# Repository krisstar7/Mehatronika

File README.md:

# GEMS Amethyst

---

- The **Proekt** folder is the **main project folder** containing all the KiCAD files you need.  
- The **Porocilo** folder holds the LaTeX source code for the report.  
- For the complete report, please check out **Mehatronika.pdf**.

---

- Mapa **Proekt** je **glavna projektna mapa**, ki vsebuje vse KiCAD datoteke.  
- Mapa **Porocilo** vsebuje LaTeX izvorno kodo za poročilo.  
- Celotno poročilo najdete v datoteki **Mehatronika.pdf**.

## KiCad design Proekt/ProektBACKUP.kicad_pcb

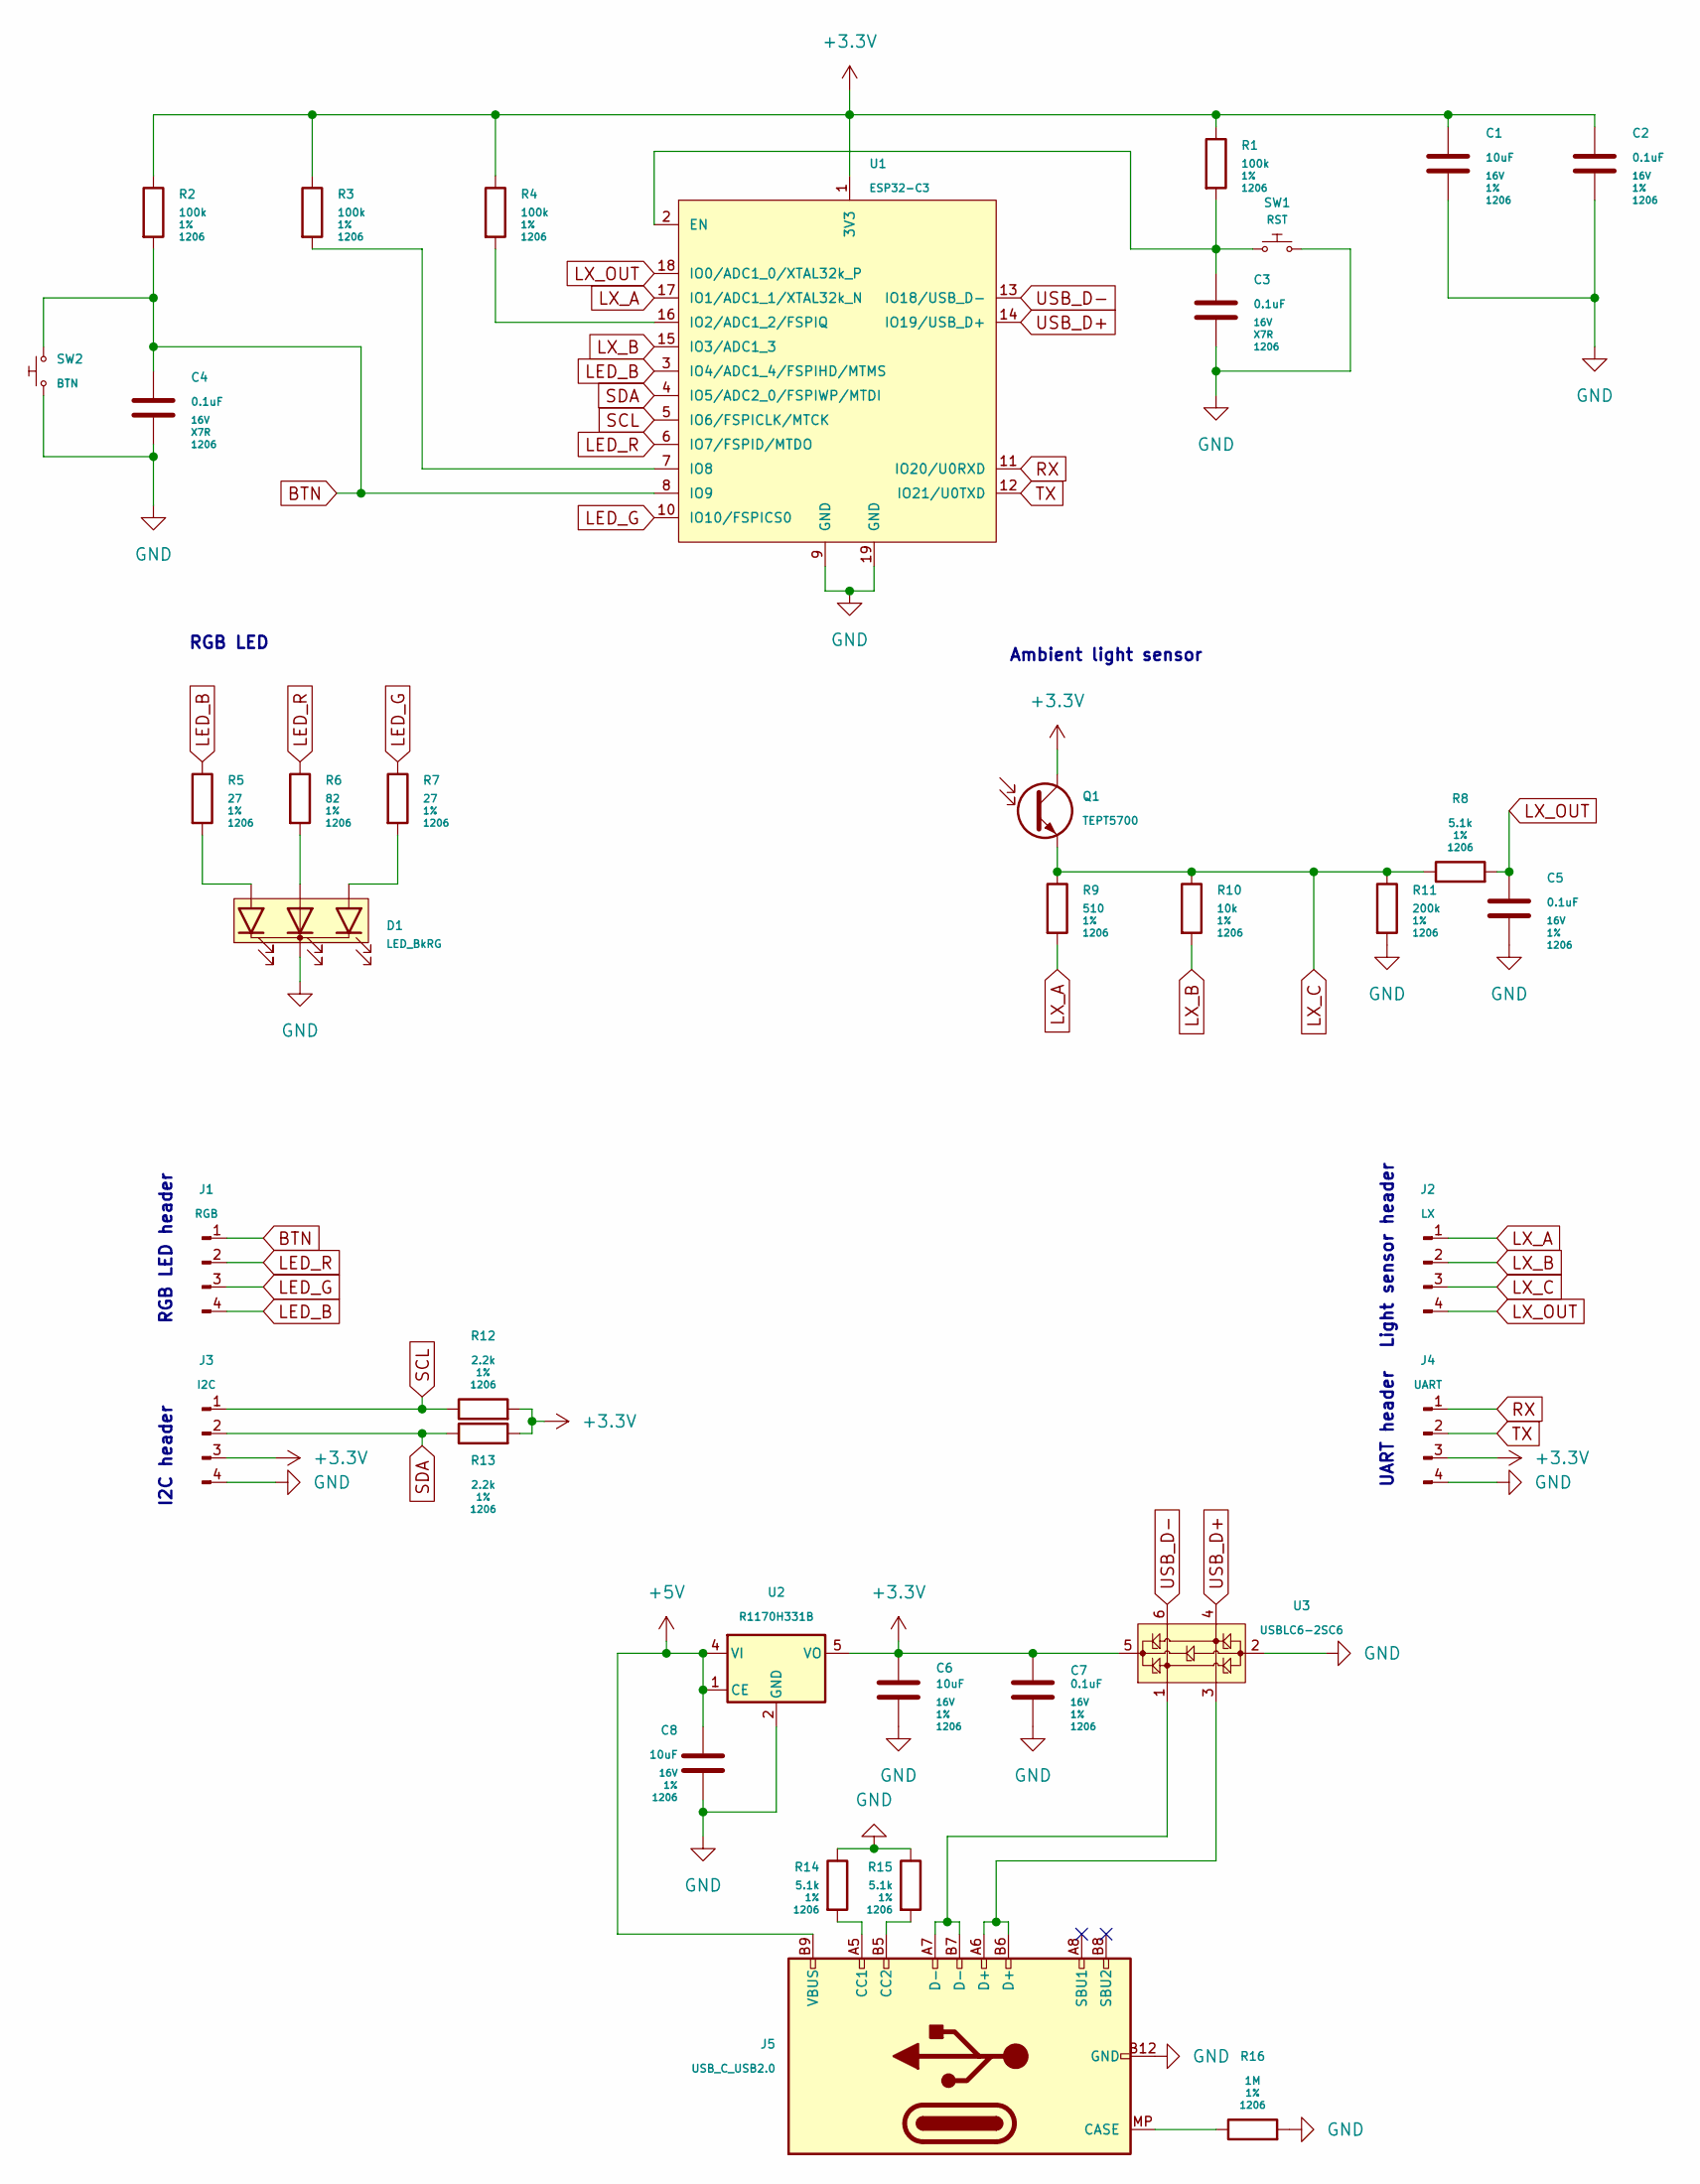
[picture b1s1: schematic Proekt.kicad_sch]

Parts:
C1, C6, C8: 10uF; C_1206_(3216); Voltage 16V; Tolerance 1%
C2, C5, C7: 0.1uF; C_1206_(3216); Voltage 16V; Tolerance 1%
C3, C4: 0.1uF; C_1206_(3216); Voltage 16V; Tolerance X7R
D1: LED_BkRG; LED_D5.0mm-4_RGB
J1: RGB; PinHeader_1x04_P2.54mm_Vertical
J2: LX; PinHeader_1x04_P2.54mm_Vertical
J3: I2C; PinHeader_1x04_P2.54mm_Vertical
J4: UART; PinHeader_1x04_P2.54mm_Vertical
J5: USB_C_USB2.0; USB-C_MOLEX-216990-0001
Q1: TEPT5700; PT_D5.0mm
R1, R2, R3, R4: 100k; R_1206_(3216); Tolerance 1%
R5, R7: 27; R_1206_(3216); Tolerance 1%
R6: 82; R_1206_(3216); Tolerance 1%
R8, R14, R15: 5.1k; R_1206_(3216); Tolerance 1%
R9: 510; R_1206_(3216); Tolerance 1%
R10: 10k; R_1206_(3216); Tolerance 1%
R11: 200k; R_1206_(3216); Tolerance 1%
R12, R13: 2.2k; R_1206_(3216); Tolerance 1%
R16: 1M; R_1206_(3216); Tolerance 1%
SW1: RST; SW_PUSH_6mm_SMD
SW2: BTN; SW_PUSH_6mm_SMD
U1: ESP32-C3; ESP32-C3-WROOM-02
U2: R1170H331B; SOT-89-5
U3: USBLC6-2SC6; SOT-23-6

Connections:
+3.3V: C1.1, C2.1, C6.1, C7.1, J3.3, J4.3, Q1.C, R1.1, R2.1, R3.1, R4.1, R12.2, R13.2, U1.1 (3V3), U2.5 (VO), U3.5 (VBUS)
+5V: C8.1, J5.A4 (VBUS), J5.A9 (VBUS), J5.B4 (VBUS), J5.B9 (VBUS), U2.1 (CE), U2.4 (VI)
BTN: C4.1, J1.1, R2.2, SW2.COM, U1.8 (IO9)
GND: C1.2, C2.2, C3.1, C4.2, C5.2, C6.2, C7.2, C8.2, D1.K, J3.4, J4.4, J5.A1 (GND), J5.A12 (GND), J5.B1 (GND), J5.B12 (GND), R11.2, R14.1, R15.1, R16.2, SW1.COM, SW2.NO, U1.9 (GND), U1.19 (GND), U2.2 (GND), U3.2 (GND)
LED_B: J1.4, R5.1, U1.3 (IO4/ADC1_4/FSPIHD/MTMS)
LED_G: J1.3, R7.1, U1.10 (IO10/FSPICS0)
LED_R: J1.2, R6.1, U1.6 (IO7/FSPID/MTDO)
LX_A: J2.1, R9.2, U1.17 (IO1/ADC1_1/XTAL32k_N)
LX_B: J2.2, R10.2, U1.15 (IO3/ADC1_3)
LX_C: J2.3, Q1.E, R8.1, R9.1, R10.1, R11.1
LX_OUT: C5.1, J2.4, R8.2, U1.18 (IO0/ADC1_0/XTAL32k_P)
unnamed: D1.Ab (Ablue), R5.2
unnamed: D1.Ag (Agreen), R7.2
unnamed: D1.Ar (Ared), R6.2
unnamed: J5.MP (CASE), R16.1
unnamed: J5.A5 (CC1), R14.2
unnamed: J5.B5 (CC2), R15.2
unnamed: J5.A6 (D+), J5.B6 (D+), U3.3 (I/O2)
unnamed: J5.A7 (D-), J5.B7 (D-), U3.1 (I/O1)
unnamed: C3.2, R1.2, SW1.NO, U1.2 (EN)
unnamed: R4.2, U1.16 (IO2/ADC1_2/FSPIQ)
unnamed: R3.2, U1.7 (IO8)
RX: J4.1, U1.11 (IO20/U0RXD)
SCL: J3.1, R12.1, U1.5 (IO6/FSPICLK/MTCK)
SDA: J3.2, R13.1, U1.4 (IO5/ADC2_0/FSPIWP/MTDI)
TX: J4.2, U1.12 (IO21/U0TXD)
USB_D+: U1.14 (IO19/USB_D+), U3.4 (I/O2)
USB_D-: U1.13 (IO18/USB_D-), U3.6 (I/O1)

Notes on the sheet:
RGB LED header
Ambient light sensor
RGB LED
Light sensor header
UART header
I2C header

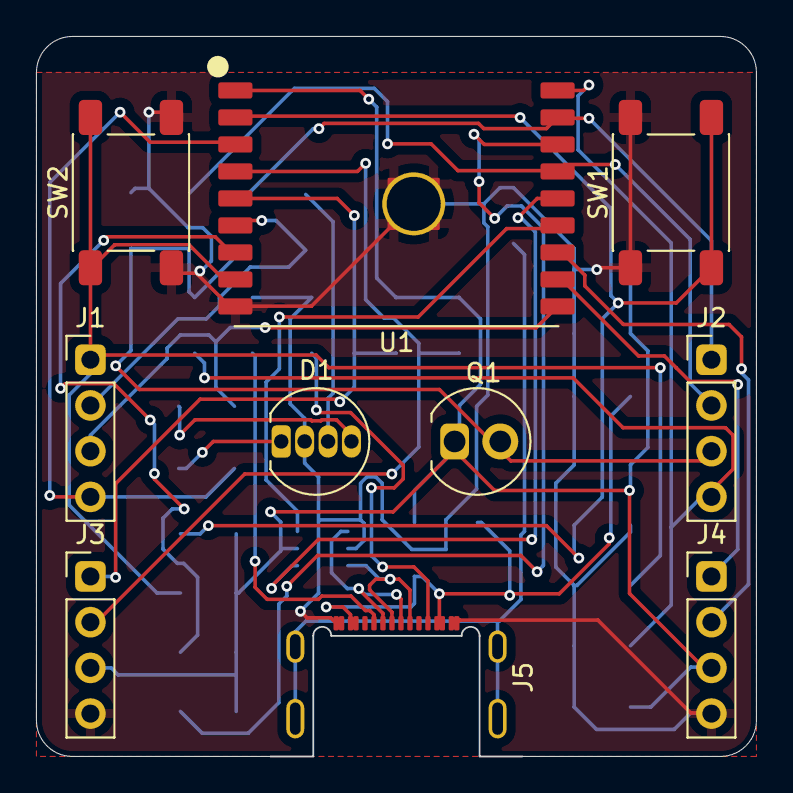
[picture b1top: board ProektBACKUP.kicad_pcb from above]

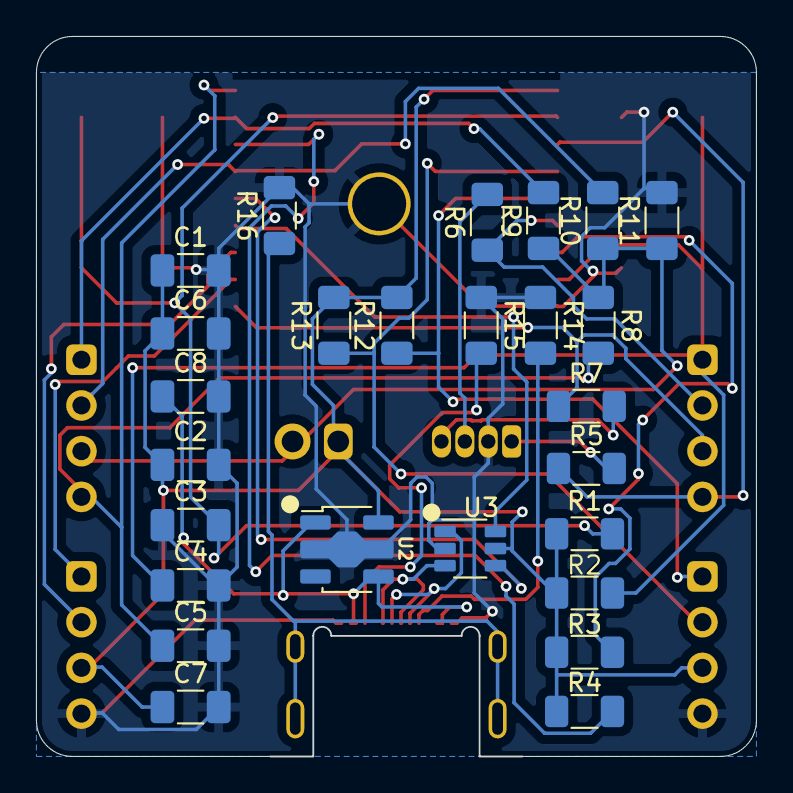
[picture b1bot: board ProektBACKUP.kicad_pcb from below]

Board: 2 copper layers, 39.9 x 40.0 mm, 36 parts (26 on the bottom side), 28 nets.

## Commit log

2025-03-10 upload scheme
2025-03-16 dodadeno pcb design
2025-03-25 dodadeno kabli
2025-05-15 dodadeno porocilo
2025-05-17 dodadeno README.md
